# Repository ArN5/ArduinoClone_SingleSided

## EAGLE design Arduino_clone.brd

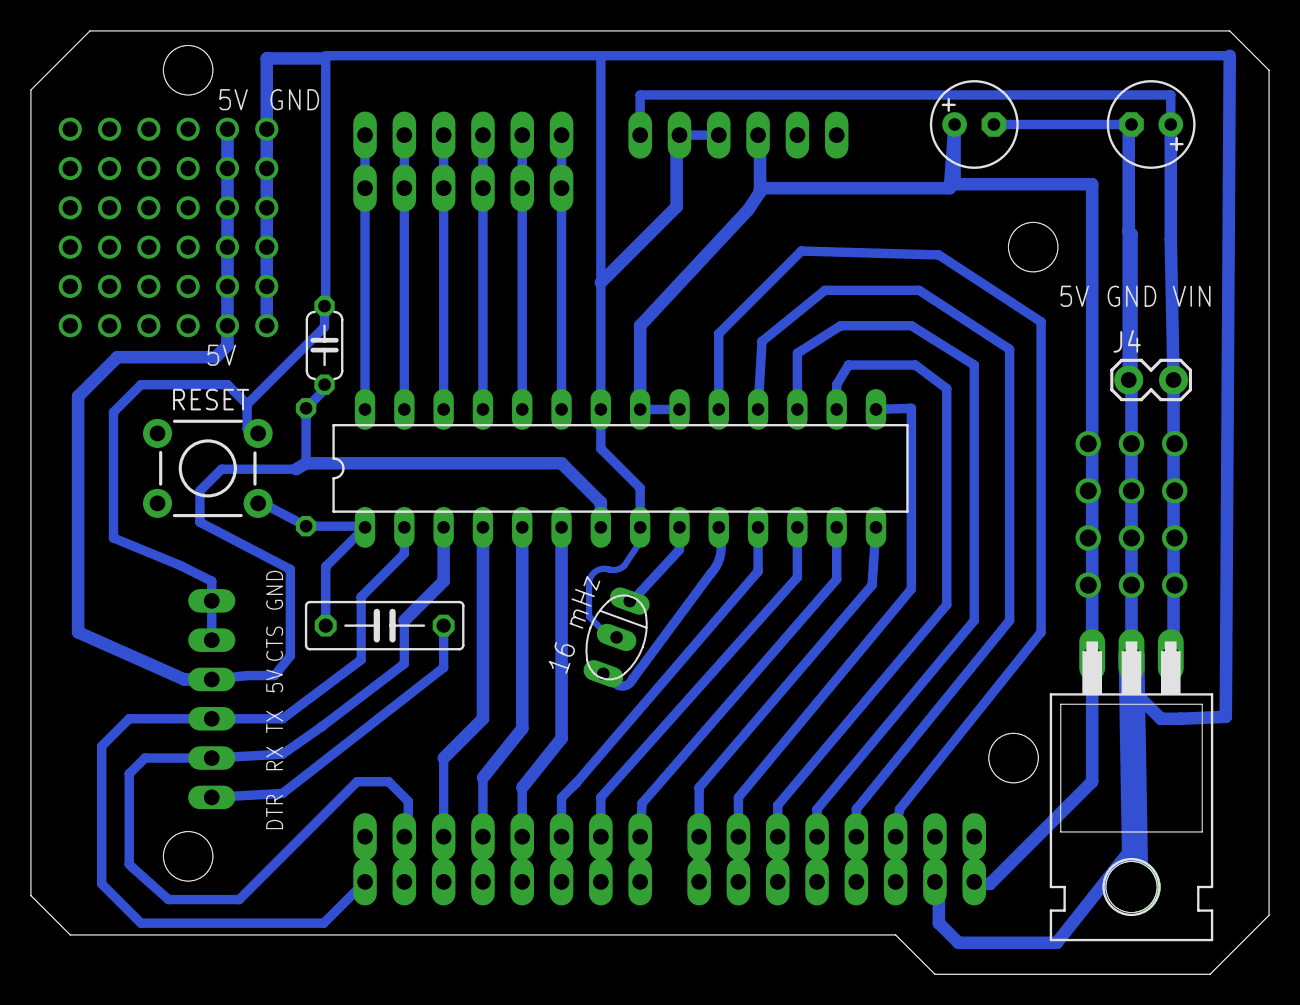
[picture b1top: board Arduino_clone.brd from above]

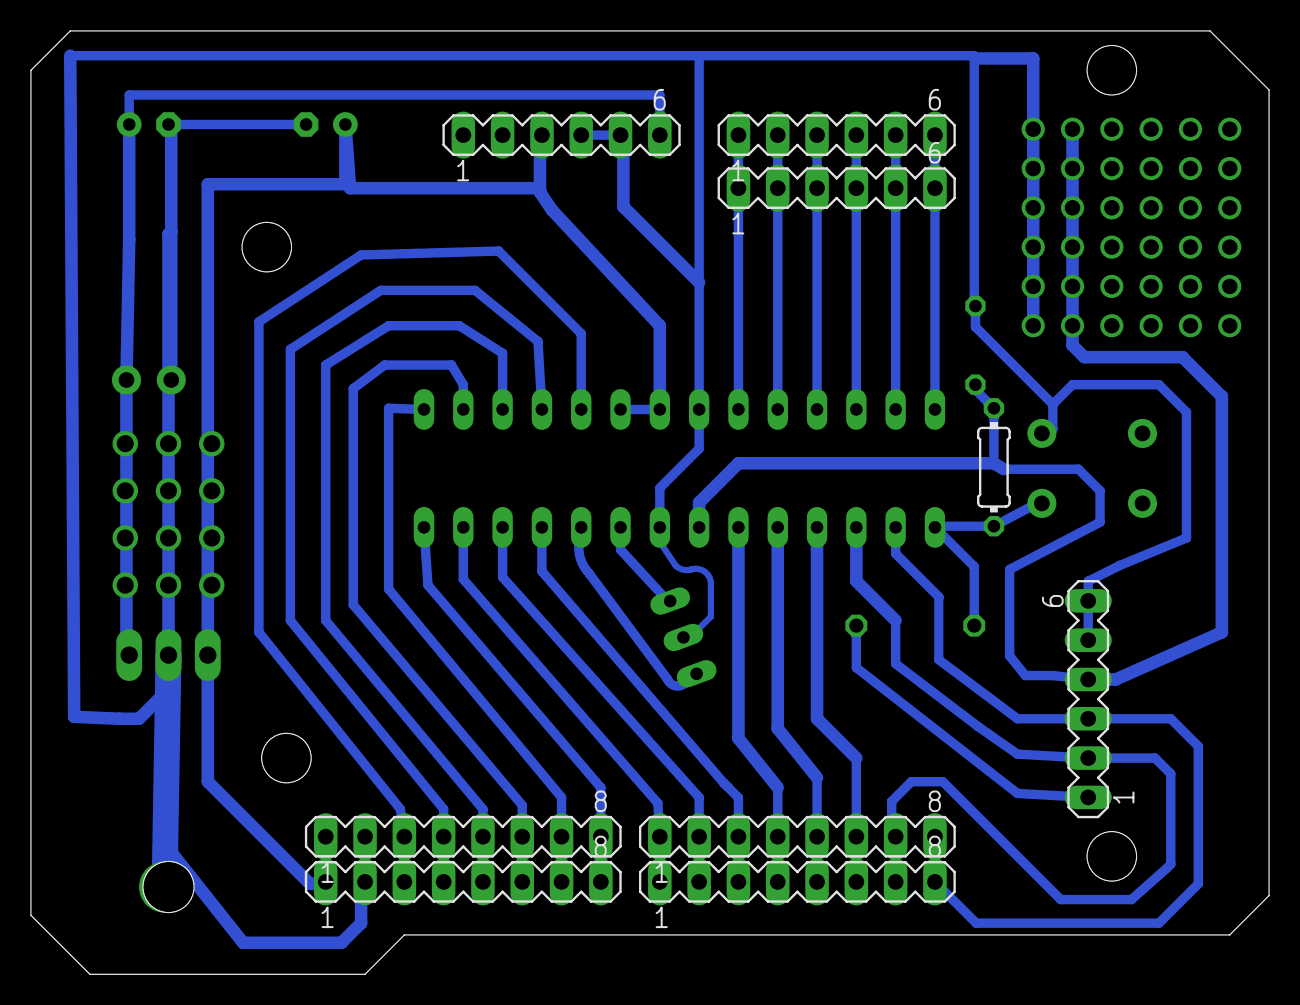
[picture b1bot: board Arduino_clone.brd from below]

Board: 2 copper layers, 80.0 x 61.0 mm, 19 parts (9 on the bottom side), 27 nets.

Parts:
C1: 220uf 10v; E2,5-6
C2: 0.1uf; C050-024X044
C3: 220uf 50v; E2,5-6
C4: 0.1uf; C075-032X103
IC1: 7805T; TO220H
IC2: ATMEGA48/88/168-PU; DIL28-3
J4: 1X02_LOCK
JP1: M01PTH_2MM; 1X01_2MM
Q1: 16 mHz; CSTLS_X
R2: 1K; 0204/7
RESET: 5501; TACTILE-PTH
SV1, SV2, SV6, SV7: MA08-1
SV3, SV4, SV5, SV8: MA06-1

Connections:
+5V: C1.+, C2.1, IC1.3, IC2.7, IC2.20, IC2.21, R2.2, SV2.1, SV3.4, SV4.3, SV6.1
A0: IC2.23, SV5.1, SV8.1
A1: IC2.24, SV5.2, SV8.2
A2: IC2.25, SV5.3, SV8.3
A3: IC2.26, SV5.4, SV8.4
A4: IC2.27, SV5.5, SV8.5
A5: IC2.28, SV5.6, SV8.6
D0: IC2.2, SV1.8, SV3.3, SV7.8
D1: IC2.3, SV1.7, SV3.2, SV7.7
D2: IC2.4, SV1.6, SV7.6
D3: IC2.5, SV1.5, SV7.5
D4: IC2.6, SV1.4, SV7.4
D5: IC2.11, SV1.3, SV7.3
D6: IC2.12, SV1.2, SV7.2
D7: IC2.13, SV1.1, SV7.1
D8: IC2.14, SV2.8, SV6.8
D9: IC2.15, SV2.7, SV6.7
D10: IC2.16, SV2.6, SV6.6
D11: IC2.17, SV2.5, SV6.5
D12: IC2.18, SV2.4, SV6.4
D13: IC2.19, SV2.3, SV6.3
GND: C1.-, C2.2, C3.-, IC1.2, IC2.8, IC2.22, J4.1, JP1.1, Q1.2, RESET.2, SV2.2, SV3.5, SV3.6, SV4.4, SV4.5, SV6.2
unnamed: C4.2, SV3.1
unnamed: IC2.10, Q1.3
unnamed: IC2.9, Q1.1
RESET: C4.1, IC2.1, R2.1, RESET.4
VIN: C3.+, IC1.1, J4.2, SV4.6

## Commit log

2016-12-13 Arduino Clone
    This board is optimized for the the othermill so it may do with a 1/32
    bit in a relatively fast time. Bare minimum Materials ATmega328p, 16MHZ
    ceramic resonator 0.1uf capacitors , Button(Short two wires if
    desperate), 1K resistor and female or male headers. If you want to use
    the voltage regulator you will need the 220uf capacitors.
2018-01-20 remove the old arduino board
    Removed a lot of useless stuff
2020-03-03 added images for the board that was made
